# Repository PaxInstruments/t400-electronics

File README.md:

t400-electronics
================

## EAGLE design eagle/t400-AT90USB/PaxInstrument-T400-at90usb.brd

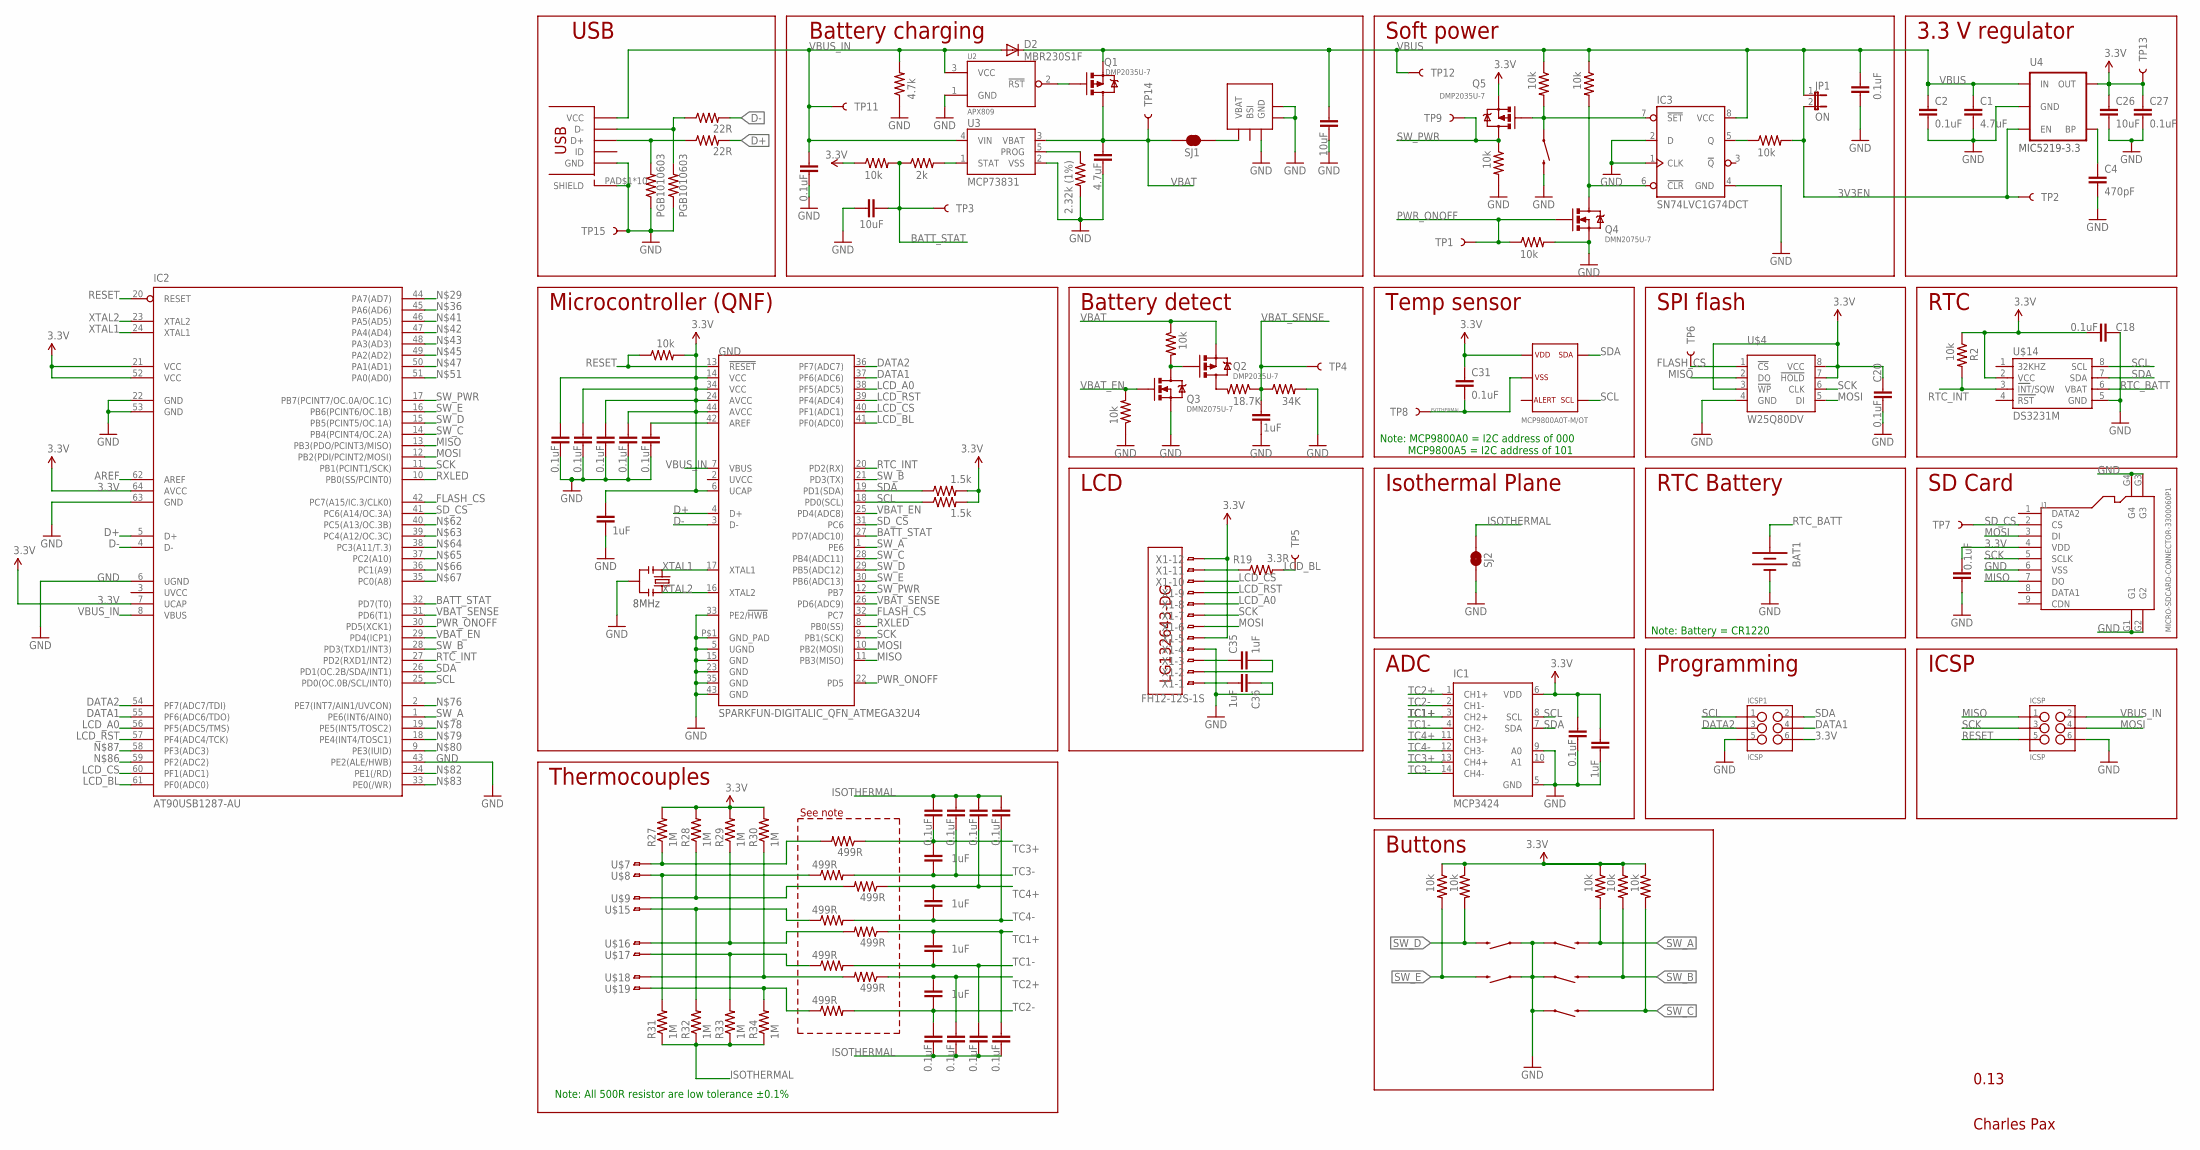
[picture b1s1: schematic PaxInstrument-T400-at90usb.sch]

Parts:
BAT1: BATTERY12MM; BATTCON_12MM; MPN 3000TR
C1, C9: 4.7uF; SPARKFUN-CAPACITORS_0603-CAP
C2, C3, C5, C6, C13, C14, C15, C16, C17, C18, C20, C21, C24, C25, C27, C28, C29, C31, C32, C33, C34, C37: 0.1uF; SPARKFUN-CAPACITORS_0603-CAP
C4: 470pF; SPARKFUN-CAPACITORS_0603-CAP
C7, C8, C10, C11, C19, C23, C30, C35, C36: 1uF; SPARKFUN-CAPACITORS_0603-CAP
C12, C22, C26: 10uF; SPARKFUN-CAPACITORS_0603-CAP
D2: MBR230S1F; SOD123; MPN MBR230S1F-7
GND: SPARKFUN-DIGITALIC_QFN_ATMEGA32U4; SPARKFUN-DIGITALIC_SPARKFUN-DIGITALIC_QFN-44; MPN ATMEGA32U4-MU
IC1: MCP3424; SO14; MPN MCP3424-E/SL
IC2: AT90USB1287-AU; TQFP64
IC3: SN74LVC1G74DCT; SSOP8; MPN SN74LVC1G74DCTR
ICSP, ICSP1: ICSP; SPARKFUN-CONNECTORS_2X3_SMT_POSTS_PAXINSTRUMENT; MPN 95278-101A06LF
J1: MICRO-SDCARD-CONNECTOR-3300060P1; 9P-SMD-W-RING; MPN ST-TF-003A
JP1: ON; SJ_2S-NO; MPN N/A
Q1, Q2, Q5: DMP2035U-7; SOT23; MPN DMP2035U-7
Q3, Q4: DMN2075U-7; SOT23; MPN DMN2075U-7
R1, R2, R4, R5, R6, R7, R8, R11, R12, R15, R16, R18, R21, R22, R23: 10k; SPARKFUN-RESISTORS_0603-RES
R3: 2.32k (1%); SPARKFUN-RESISTORS_0603-RES
R9, R10: 22R; SPARKFUN-RESISTORS_0603-RES
R13, R14: 1.5k; SPARKFUN-RESISTORS_0603-RES
R17: 2k; SPARKFUN-RESISTORS_0603-RES
R19: 3.3R; SPARKFUN-RESISTORS_0603-RES
R20: 18.7K; SPARKFUN-RESISTORS_0603-RES
R24: 34K; SPARKFUN-RESISTORS_0603-RES
R25: 4.7k; SPARKFUN-RESISTORS_0603-RES
R27, R28, R29, R30, R31, R32, R33, R34: 1M; SPARKFUN-RESISTORS_0603-RES
R35, R36, R37, R38, R39, R40, R41, R42: 499R; SPARKFUN-RESISTORS_0603-RES; MPN TNPW0603499RBEEA
S1, S2, S3, S4, S5, S6: SWITCH-MOMENTARY-2SMD; TACTILE_SWITCH_SMD; MPN RS-187R05A2-DS MT RT
SJ1, SJ2: JUMPER-PAD-2-NC_BY_TRACE; PAD-JUMPER-2-NC_BY_TRACE_YES_SILK; MPN N/A
TP1: PWR_ONOFF; TP_15TH; MPN N/A
TP2: 3V3_EN; TP_15TH; MPN N/A
TP3: BATT_STAT; TP_15TH; MPN N/A
TP4: VBAT_SENSE; TP_15TH; MPN N/A
TP5: LCD_BL; TP_15TH; MPN N/A
TP6: FLASH_CS; TP_15TH; MPN N/A
TP7: SD_CS; TP_15TH; MPN N/A
TP8: ISOTHERMAL; TP_15TH; MPN N/A
TP9: SW_PWR; TP_15TH; MPN N/A
TP11: VBUS_IN; TP_15TH; MPN N/A
TP12: VBUS; TP_15TH; MPN N/A
TP13: 3.3V; TP_15TH; MPN N/A
TP14: VBAT; TP_15TH; MPN N/A
TP15: GND; TP_15TH; MPN N/A
U1: MCP9800; SOT23-5L; MPN MCP9800A0T-M/OT
U2: APX809; SOT23; MPN APX809-44SAG-7
U3: MCP73831; SOT23-5; MPN MCP73832T-2DCI/OT
U4: MIC5219-3.3V; SOT23-5; MPN MIC5219-3.3YM5 TR
U$1: USB_MICROSMT+THRUHULE; USB_MICRO_THRUHOLE; MPN 10118194-0001LF
U$2: BL-5C-CONNECTOR; MPN BC-4-3P (77H)
U$4: W25Q80DV; CHARLESPAX_SOIC8M; MPN W25Q80DVSSIG-ND
U$5: LG132643-DG; MPN LG132643-DW
U$7, U$8, U$9, U$15, U$16, U$17, U$18, U$19: TC-MINI-SINGLE; TC-CLIP-SINGLE
U$14: DS3231M; SOIC8; MPN DS3231MZ+
X1: FH12-12S-1S; FH12-12S-1SH; MPN FH12-12S-1SH(55)
Y1: RESONATORSMD; RESONATOR-SMD; MPN CSTCE8M00G52-R0
Z1, Z2: PGB1010603; SPARKFUN-RESISTORS_0603-RES; MPN PGB1010603NRHF

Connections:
3.3V: C5.1, C18.1, C19.1, C20.2, C21.2, C26.1, C27.1, C29.1, C30.1, C31.1, C32.1, C33.1, C34.1, GND.6 (UCAP), GND.14 (VCC), GND.24 (AVCC), GND.34 (VCC), GND.44 (AVCC), IC1.6 (VDD), IC2.7 (UCAP), IC2.21 (VCC), IC2.52 (VCC), IC2.64 (AVCC), ICSP1.6, J1.4 (VDD), Q5.2 (S), R1.1, R2.1, R4.2, R8.1, R11.1, R12.1, R13.2, R14.2, R15.1, R16.1, R27.2, R28.2, R29.2, R30.2, TP13.P$1, U1.1, U4.5 (OUT), U$4.3 (!WP), U$4.7 (!HOLD), U$4.8 (VCC), U$14.2 (VCC), X1.5, X1.12
3V3EN: JP1.2, R21.2, TP2.P$1, U4.3 (EN)
AREF: C3.1, GND.42 (AREF), IC2.62 (AREF)
BATT_STAT: C22.1, GND.27 (PD7(ADC10)), IC2.32 (PD7(T0)), R1.2, R17.1, TP3.P$1
D+: GND.4 (D+), IC2.5 (D+), R9.2
D-: GND.3 (D-), IC2.4 (D-), R10.2
DATA1: GND.37 (PF6(ADC6)), IC2.55 (PF6(ADC6/TDO)), ICSP1.4
DATA2: GND.36 (PF7(ADC7)), IC2.54 (PF7(ADC7/TDI)), ICSP1.3
FLASH_CS: GND.32 (PC7), IC2.42 (PC7(A15/IC.3/CLK0)), TP6.P$1, U$4.1 (!CS)
GND: BAT1.GND (-), C1.2, C2.2, C3.2, C4.2, C5.2, C6.2, C9.2, C12.2, C18.2, C19.2, C20.1, C21.1, C22.2, C23.2, C26.2, C27.2, C28.2, C29.2, C30.2, C32.2, C33.2, C34.2, C36.1, GND.5 (UGND), GND.15 (GND), GND.23 (GND), GND.33 (PE2/!HWB), GND.35 (GND), GND.43 (GND), GND.P$1 (GND_PAD), IC1.5 (GND), IC1.9 (A0), IC2.6 (UGND), IC2.22 (GND), IC2.43 (PE2(ALE/HWB)), IC2.53 (GND), IC2.63 (GND), IC3.1 (CLK), IC3.2 (D), IC3.4 (GND), ICSP.6, ICSP1.5, J1.6 (VSS), J1.G1, J1.G2, J1.G3, J1.G4, Q3.2 (S), Q4.2 (S), R3.2, R18.2, R22.2, R23.1, R24.2, R25.1, S1.1, S2.1, S3.1, S4.1, S5.1, S6.3 (2), SJ2.1, TP15.P$1, U2.1 (GND), U3.2 (VSS), U4.2 (GND), U$1.PAD$1 (SHIELD), U$1.PAD$2 (SHIELD), U$1.PAD$3 (SHIELD), U$1.PAD$4 (SHIELD), U$1.PAD$5 (SHIELD), U$1.PAD$6 (SHIELD), U$1.PAD$7 (SHIELD), U$1.PAD$8 (SHIELD), U$1.PAD$9 (SHIELD), U$1.PAD$10 (SHIELD), U$1.PIN$5 (GND), U$2.P$3 (GND), U$2.P$4, U$2.P$5, U$4.4 (GND), U$14.5 (GND), X1.4, Y1.2, Z1.1, Z2.1
ISOTHERMAL: C13.2, C14.2, C15.2, C16.2, C17.1, C24.1, C25.1, C31.2, C37.1, R31.1, R32.1, R33.1, R34.1, SJ2.2, TP8.P$1, U1.2
LCD_A0: GND.38 (PF5(ADC5)), IC2.56 (PF5(ADC5/TMS)), X1.8
LCD_BL: GND.41 (PF0(ADC0)), IC2.61 (PF0(ADC0)), R19.2, TP5.P$1
LCD_CS: GND.40 (PF1(ADC1)), IC2.60 (PF1(ADC1)), X1.10
LCD_RST: GND.39 (PF4(ADC4)), IC2.57 (PF4(ADC4/TCK)), X1.9
MISO: GND.11 (PB3(MISO)), IC2.13 (PB3(PDO/PCINT3/MISO)), ICSP.1, J1.7 (DO), U$4.2 (DO)
MOSI: GND.10 (PB2(MOSI)), IC2.12 (PB2(PDI/PCINT2/MOSI)), ICSP.4, J1.3 (DI), U$4.5 (DI), X1.6
unnamed: C4.1, U4.4 (BP)
unnamed: R17.2, U3.1 (STAT)
unnamed: R19.1, X1.11
unnamed: R31.2, R36.1, U$8.P$1
unnamed: R3.1, U3.5 (PROG)
unnamed: SJ1.2, U$2.P$1 (VBAT)
unnamed: R27.1, R35.2, U$7.P$1
unnamed: Q1.1 (G), U2.2 (!RST)
unnamed: R29.1, R39.2, U$16.P$1
unnamed: R33.2, R41.1, U$17.P$1
unnamed: R34.2, R42.1, U$19.P$1
unnamed: Q2.3 (D), R20.2
unnamed: IC3.7 (!SET), Q5.1 (G), R6.2, S6.1
unnamed: Q2.1 (G), Q3.3 (D), R5.2
unnamed: IC3.6 (!CLR), Q4.3 (D), R7.2
unnamed: IC3.5 (Q), R21.1
unnamed: R10.1, U$1.PIN$2 (D-), Z2.2
unnamed: R9.1, U$1.PIN$3 (D+), Z1.2
unnamed: R32.2, R38.1, U$15.P$1
unnamed: R28.1, R37.2, U$9.P$1
unnamed: C35.1, X1.3
unnamed: C35.2, X1.2
unnamed: C36.2, X1.1
unnamed: R30.1, R40.2, U$18.P$1
PWR_ONOFF: GND.22 (PD5), IC2.30 (PD5(XCK1)), Q4.1 (G), R22.1, TP1.P$1
RESET: GND.13 (!RESET), IC2.20 (RESET), ICSP.5, R4.1
RTC_BATT: BAT1.PWR@1 (+), U$14.6 (VBAT)
RTC_INT: GND.20 (PD2(RX)), IC2.27 (PD2(RXD1/INT2)), R2.2, U$14.3 (INT/SQW)
RXLED: GND.8 (PB0(SS)), IC2.10 (PB0(SS/PCINT0))
SCK: GND.9 (PB1(SCK)), IC2.11 (PB1(PCINT1/SCK)), ICSP.3, J1.5 (SCLK), U$4.6 (CLK), X1.7
SCL: GND.18 (PD0(SCL)), IC1.8 (SCL), IC2.25 (PD0(OC.0B/SCL/INT0)), ICSP1.1, R14.1, U1.4, U$14.8 (SCL)
SDA: GND.19 (PD1(SDA)), IC1.7 (SDA), IC2.26 (PD1(OC.2B/SDA/INT1)), ICSP1.2, R13.1, U1.5, U$14.7 (SDA)
SD_CS: GND.31 (PC6), IC2.41 (PC6(A14/OC.3A)), J1.2 (CS), TP7.P$1
SW_A: GND.1 (PE6), IC2.1 (PE6(INT6/AIN0)), R8.2, S3.3 (2)
SW_B: GND.21 (PD3(TX)), IC2.28 (PD3(TXD1/INT3)), R11.2, S2.3 (2)
SW_C: GND.28 (PB4(ADC11)), IC2.14 (PB4(PCINT4/OC.2A)), R12.2, S1.3 (2)
SW_D: GND.29 (PB5(ADC12)), IC2.15 (PB5(PCINT5/OC.1A)), R15.2, S4.3 (2)
SW_E: GND.30 (PB6(ADC13)), IC2.16 (PB6(PCINT6/OC.1B)), R16.2, S5.3 (2)
SW_PWR: GND.12 (PB7), IC2.17 (PB7(PCINT7/OC.0A/OC.1C)), Q5.3 (D), R18.1, TP9.P$1
TC1+: C10.1, C16.1, IC1.3 (CH2+), R39.1
TC1-: C10.2, C15.1, IC1.4 (CH2-), R41.2
TC2+: C11.1, C14.1, IC1.1 (CH1+), R40.1
TC2-: C11.2, C13.1, IC1.2 (CH1-), R42.2
TC3+: C7.1, C17.2, IC1.13 (CH4+), R35.1
TC3-: C7.2, C24.2, IC1.14 (CH4-), R36.2
TC4+: C8.1, C25.2, IC1.11 (CH3+), R37.1
TC4-: C8.2, C37.2, IC1.12 (CH3-), R38.2
UVCC: IC2.3 (UVCC)
VBAT: C9.1, Q1.3 (D), Q2.2 (S), R5.1, SJ1.1, TP14.P$1, U3.3 (VBAT)
VBAT_EN: GND.25 (PD4(ADC8)), IC2.29 (PD4(ICP1)), Q3.1 (G), R23.2
VBAT_SENSE: C23.1, GND.26 (PD6(ADC9)), IC2.31 (PD6(T1)), R20.1, R24.1, TP4.P$1
VBUS: C1.1, C2.1, C12.1, C28.1, D2.C, IC3.8 (VCC), JP1.1, Q1.2 (S), R6.1, R7.1, TP12.P$1, U4.1 (IN)
VBUS_IN: C6.1, D2.A, GND.7 (VBUS), IC2.8 (VBUS), ICSP.2, R25.2, TP11.P$1, U2.3 (VCC), U3.4 (VIN), U$1.PIN$1 (VCC)
XTAL1: GND.17 (XTAL1), IC2.24 (XTAL1), Y1.1
XTAL2: GND.16 (XTAL2), IC2.23 (XTAL2), Y1.3

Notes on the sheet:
MIC5219-3.3
8MHz
ADC
USB
Battery charging
Soft power
3.3 V regulator
RTC
LCD
Buttons
Microcontroller (QNF)
ICSP
Temp sensor
0.13
Programming
Isothermal Plane
Thermocouples
RTC Battery
Charles Pax
SPI flash
SD Card
Battery detect
Note: MCP9800A0 = I2C address of 000 MCP9800A5 = I2C address of 101
Note: All 500R resistor are low tolerance ±0.1%
See note
Note: Battery = CR1220

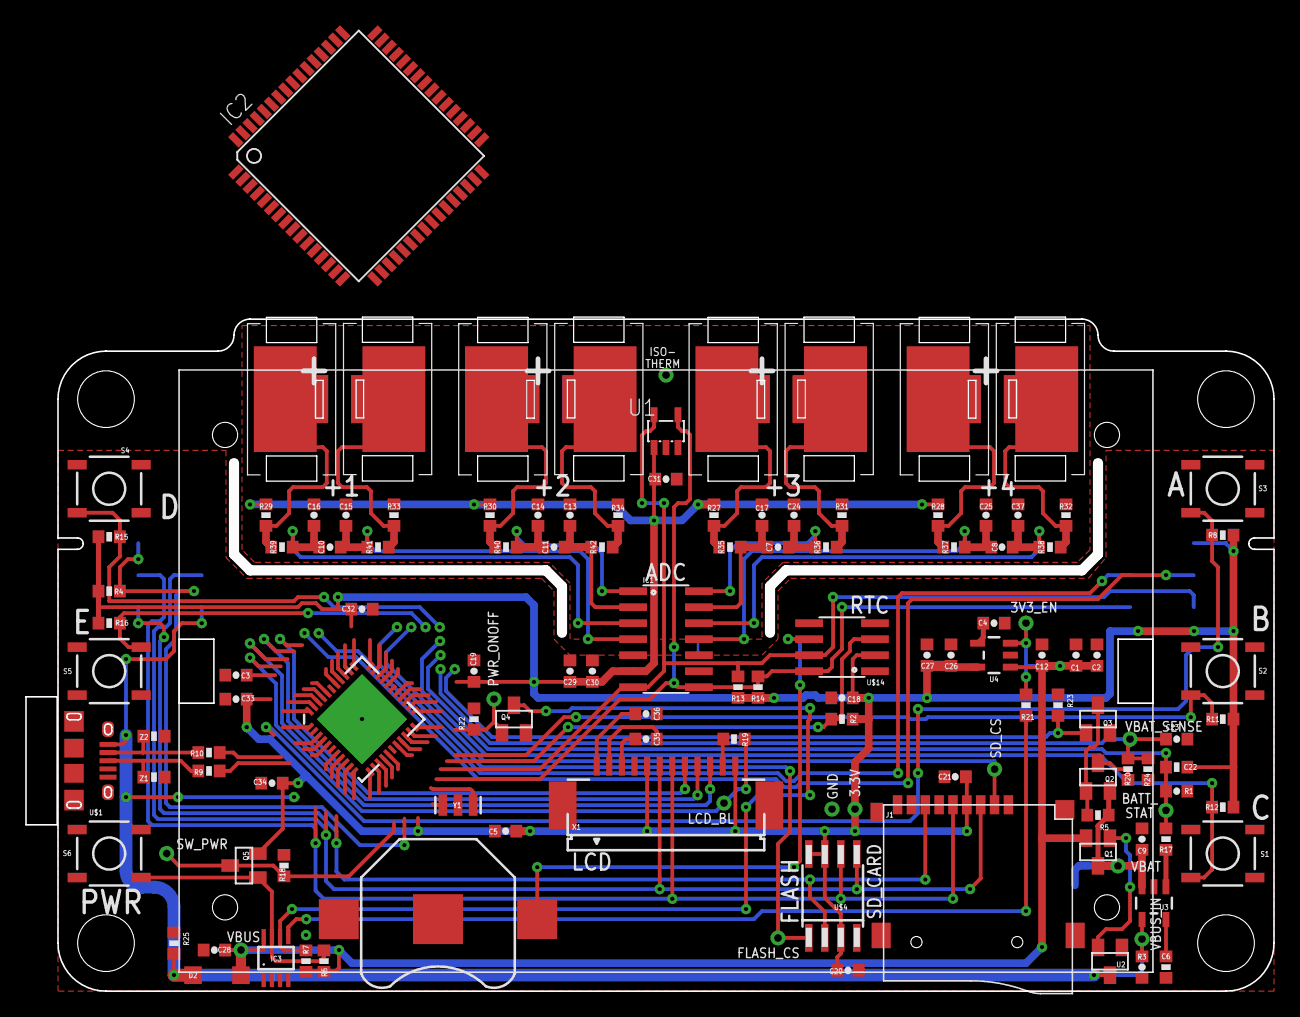
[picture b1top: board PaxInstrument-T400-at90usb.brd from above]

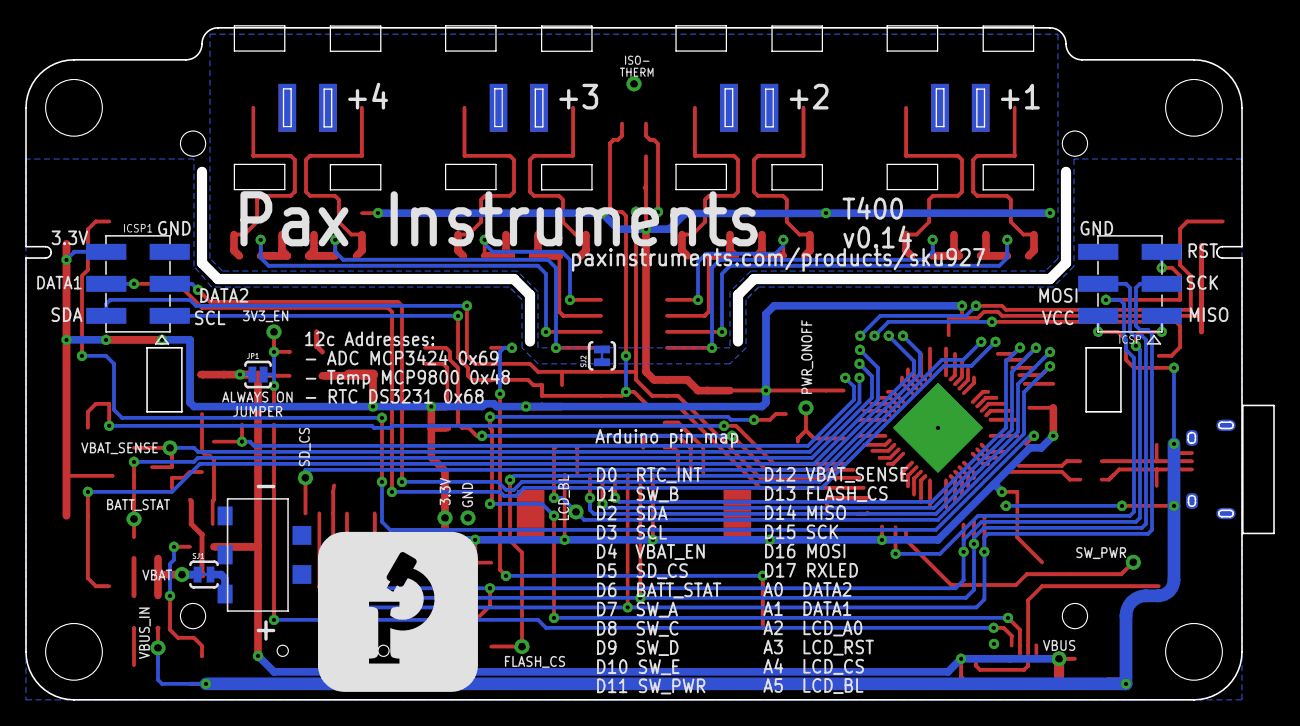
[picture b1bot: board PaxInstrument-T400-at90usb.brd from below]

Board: 4 copper layers, 99.1 x 53.5 mm, 137 parts (11 on the bottom side), 71 nets.

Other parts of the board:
U$6: PAX-LOGO-0.5IN

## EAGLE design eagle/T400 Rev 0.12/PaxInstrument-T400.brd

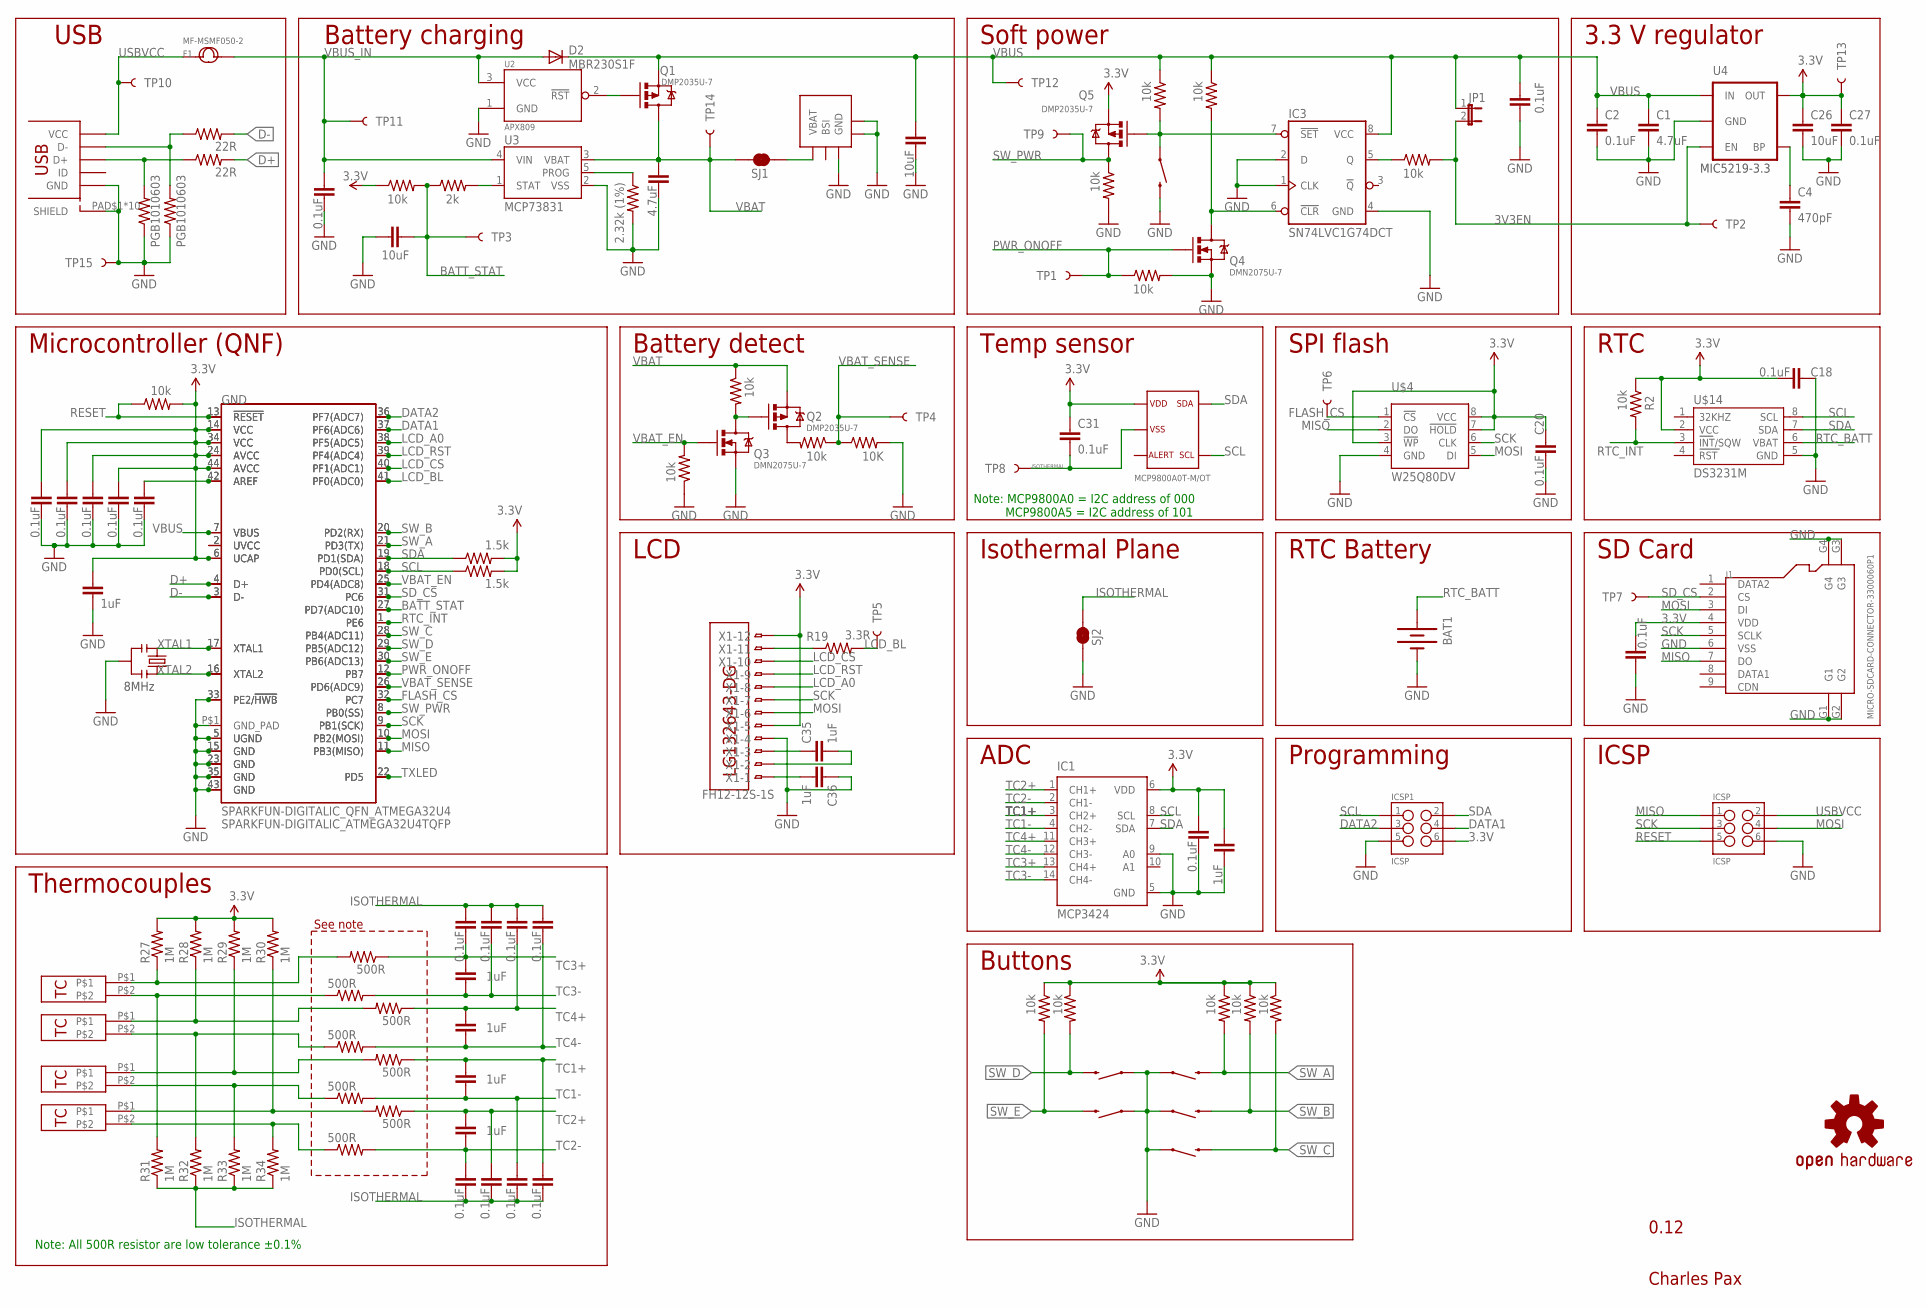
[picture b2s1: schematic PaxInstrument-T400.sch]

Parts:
BAT1: BATTERY12MM; BATTCON_12MM; MPN 3000TR
C1, C9: 4.7uF; SPARKFUN-CAPACITORS_0603-CAP
C2, C3, C5, C6, C13, C14, C15, C16, C17, C18, C20, C21, C24, C25, C27, C28, C29, C31, C32, C33, C34, C37: 0.1uF; SPARKFUN-CAPACITORS_0603-CAP
C4: 470pF; SPARKFUN-CAPACITORS_0603-CAP
C7, C8, C10, C11, C19, C30, C35, C36: 1uF; SPARKFUN-CAPACITORS_0603-CAP
C12, C22, C26: 10uF; SPARKFUN-CAPACITORS_0603-CAP
D2: MBR230S1F; SOD123; MPN MBR230S1F-7
F1: FUSE-1812; F1812; MPN MF-MSMF050-2
GND: SPARKFUN-DIGITALIC_QFN_ATMEGA32U4; SPARKFUN-DIGITALIC_SPARKFUN-DIGITALIC_QFN-44; MPN ATMEGA32U4-MU
IC1: MCP3424; SO14; MPN MCP3424-E/SL
IC3: SN74LVC1G74DCT; SSOP8; MPN SN74LVC1G74DCTR
ICSP, ICSP1: ICSP; SPARKFUN-CONNECTORS_2X3_SMT_POSTS_PAXINSTRUMENT; MPN 95278-101A06LF
J1: MICRO-SDCARD-CONNECTOR-3300060P1; 9P-SMD-W-RING; MPN ST-TF-003A
JP1: JUMPER-2SMD-NO; SJ_2S-NO; MPN N/A
LOGO1: OSHW-LOGOS; OSHW-LOGO-S; MPN N/A
Q1, Q2, Q5: DMP2035U-7; SOT23; MPN DMP2035U-7
Q3, Q4: DMN2075U-7; SOT23; MPN DMN2075U-7
R1, R2, R4, R5, R6, R7, R8, R11, R12, R15, R16, R18, R20, R21, R22, R23: 10k; SPARKFUN-RESISTORS_0603-RES
R3: 2.32k (1%); SPARKFUN-RESISTORS_0603-RES
R9, R10: 22R; SPARKFUN-RESISTORS_0603-RES
R13, R14: 1.5k; SPARKFUN-RESISTORS_0603-RES
R17: 2k; SPARKFUN-RESISTORS_0603-RES
R19: 3.3R; SPARKFUN-RESISTORS_0603-RES
R24: 10K; SPARKFUN-RESISTORS_0603-RES
R27, R28, R29, R30, R31, R32, R33, R34: 1M; SPARKFUN-RESISTORS_0603-RES
R35, R36, R37, R38, R39, R40, R41, R42: 500R; SPARKFUN-RESISTORS_0603-RES; MPN RN732ATTD5000B25
S1, S2, S3, S4, S5, S6: SWITCH-MOMENTARY-2SMD; TACTILE_SWITCH_SMD; MPN RS-187R05A2-DS MT RT
SJ1, SJ2: JUMPER-PAD-2-NC_BY_TRACE; PAD-JUMPER-2-NC_BY_TRACE_YES_SILK; MPN N/A
TP1: PWR_ONOFF; TP_15TH; MPN N/A
TP2: 3V3_EN; TP_15TH; MPN N/A
TP3: BATT_STAT; TP_15TH; MPN N/A
TP4: VBAT_SENSE; TP_15TH; MPN N/A
TP5: LCD_BL; TP_15TH; MPN N/A
TP6: FLASH_CS; TP_15TH; MPN N/A
TP7: SD_CS; TP_15TH; MPN N/A
TP8: ISOTHERMAL; TP_15TH; MPN N/A
TP9: SW_PWR; TP_15TH; MPN N/A
TP10: TEST-POINTTP_15TH_THRU; TP_15TH; MPN N/A
TP11: VBUS_IN; TP_15TH; MPN N/A
TP12: VBUS; TP_15TH; MPN N/A
TP13: 3.3V; TP_15TH; MPN N/A
TP14: VBAT; TP_15TH; MPN N/A
TP15: GND; TP_15TH; MPN N/A
U1: MCP9800; SOT23-5L; MPN MCP9800A0T-M/OT
U2: APX809; SOT23; MPN APX809-44SAG-7
U3: MCP73831; SOT23-5; MPN MCP73832T-2DCI/OT
U4: MIC5219-3.3V; SOT23-5; MPN MIC5219-3.3YM5 TR
U$1: USB_MICROSMT+THRUHULE; USB_MICRO_THRUHOLE; MPN 10118194-0001LF
U$2: BL-5C-CONNECTOR
U$3: SPARKFUN-DIGITALIC_ATMEGA32U4TQFP; SPARKFUN-DIGITALIC_SPARKFUN-DIGITALIC_TQFP44; MPN ATMEGA32U4-AU
U$4: W25Q80DV; CHARLESPAX_SOIC8M; MPN W25Q80DVSSIG-ND
U$5: LG132643-DG; MPN LG132643-DW
U$10, U$11, U$12, U$13: CHARLESPAX_TC-MINI-CONNECTOR; MPN 3572
U$14: DS3231M; SOIC8; MPN DS3231MZ+
X1: FH12-12S-1S; FH12-12S-1SH; MPN FH12-12S-1SH(55)
Y1: RESONATORSMD; RESONATOR-SMD; MPN CSTCE8M00G52-R0
Z1, Z2: PGB1010603; SPARKFUN-RESISTORS_0603-RES; MPN PGB1010603NRHF

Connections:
3.3V: C5.1, C18.1, C19.1, C20.2, C21.2, C26.1, C27.1, C29.1, C30.1, C31.1, C32.1, C33.1, C34.1, GND.6 (UCAP), GND.14 (VCC), GND.24 (AVCC), GND.34 (VCC), GND.44 (AVCC), IC1.6 (VDD), ICSP1.6, J1.4 (VDD), Q5.2 (S), R1.1, R2.1, R4.2, R8.1, R11.1, R12.1, R13.2, R14.2, R15.1, R16.1, R27.2, R28.2, R29.2, R30.2, TP13.P$1, U1.1, U4.5 (OUT), U$3.6 (UCAP), U$3.14 (VCC), U$3.24 (AVCC), U$3.34 (VCC), U$3.44 (AVCC), U$4.3 (!WP), U$4.7 (!HOLD), U$4.8 (VCC), U$14.2 (VCC), X1.5, X1.12
3V3EN: JP1.2, R21.2, TP2.P$1, U4.3 (EN)
BATT_STAT: C22.1, GND.27 (PD7(ADC10)), R1.2, R17.1, TP3.P$1, U$3.27 (PD7(ADC10))
D+: GND.4 (D+), R9.2, U$3.4 (D+)
D-: GND.3 (D-), R10.2, U$3.3 (D-)
DATA1: GND.37 (PF6(ADC6)), ICSP1.4, U$3.37 (PF6(ADC6))
DATA2: GND.36 (PF7(ADC7)), ICSP1.3, U$3.36 (PF7(ADC7))
FLASH_CS: GND.32 (PC7), TP6.P$1, U$3.32 (PC7), U$4.1 (!CS)
GND: BAT1.GND (-), C1.2, C2.2, C3.2, C4.2, C5.2, C6.2, C9.2, C12.2, C18.2, C19.2, C20.1, C21.1, C22.2, C26.2, C27.2, C28.2, C29.2, C30.2, C32.2, C33.2, C34.2, C36.1, GND.5 (UGND), GND.15 (GND), GND.23 (GND), GND.33 (PE2/!HWB), GND.35 (GND), GND.43 (GND), GND.P$1 (GND_PAD), IC1.5 (GND), IC1.9 (A0), IC3.1 (CLK), IC3.2 (D), IC3.4 (GND), ICSP.6, ICSP1.5, J1.6 (VSS), J1.G1, J1.G2, J1.G3, J1.G4, Q3.2 (S), Q4.2 (S), R3.2, R18.2, R22.2, R23.1, R24.2, S1.1, S2.1, S3.1, S4.1, S5.1, S6.3 (2), SJ2.1, TP15.P$1, U2.1 (GND), U3.2 (VSS), U4.2 (GND), U$1.PAD$1 (SHIELD), U$1.PAD$2 (SHIELD), U$1.PAD$3 (SHIELD), U$1.PAD$4 (SHIELD), U$1.PAD$5 (SHIELD), U$1.PAD$6 (SHIELD), U$1.PAD$7 (SHIELD), U$1.PAD$8 (SHIELD), U$1.PAD$9 (SHIELD), U$1.PAD$10 (SHIELD), U$1.PIN$5 (GND), U$2.P$3 (GND), U$2.P$4, U$2.P$5, U$3.5 (UGND), U$3.15 (GND), U$3.23 (GND), U$3.33 (PE2/!HWB), U$3.35 (GND), U$3.43 (GND), U$4.4 (GND), U$14.5 (GND), X1.4, Y1.2, Z1.1, Z2.1
ISOTHERMAL: C13.2, C14.2, C15.2, C16.2, C17.1, C24.1, C25.1, C31.2, C37.1, R31.1, R32.1, R33.1, R34.1, SJ2.2, TP8.P$1, U1.2
LCD_A0: GND.38 (PF5(ADC5)), U$3.38 (PF5(ADC5)), X1.8
LCD_BL: GND.41 (PF0(ADC0)), R19.2, TP5.P$1, U$3.41 (PF0(ADC0))
LCD_CS: GND.40 (PF1(ADC1)), U$3.40 (PF1(ADC1)), X1.10
LCD_RST: GND.39 (PF4(ADC4)), U$3.39 (PF4(ADC4)), X1.9
MISO: GND.11 (PB3(MISO)), ICSP.1, J1.7 (DO), U$3.11 (PB3(MISO)), U$4.2 (DO)
MOSI: GND.10 (PB2(MOSI)), ICSP.4, J1.3 (DI), U$3.10 (PB2(MOSI)), U$4.5 (DI), X1.6
unnamed: C4.1, U4.4 (BP)
unnamed: R17.2, U3.1 (STAT)
unnamed: R19.1, X1.11
unnamed: R31.2, R36.1, U$10.P$2
unnamed: R3.1, U3.5 (PROG)
unnamed: SJ1.2, U$2.P$1 (VBAT)
unnamed: R27.1, R35.2, U$10.P$1
unnamed: Q1.1 (G), U2.2 (!RST)
unnamed: R29.1, R39.2, U$12.P$1
unnamed: R33.2, R41.1, U$12.P$2
unnamed: C3.1, GND.42 (AREF), U$3.42 (AREF)
unnamed: R34.2, R42.1, U$13.P$2
unnamed: GND.2 (UVCC), U$3.2 (UVCC)
unnamed: Q2.3 (D), R20.2
unnamed: IC3.7 (!SET), Q5.1 (G), R6.2, S6.1
unnamed: Q2.1 (G), Q3.3 (D), R5.2
unnamed: IC3.6 (!CLR), Q4.3 (D), R7.2
unnamed: IC3.5 (Q), R21.1
unnamed: R10.1, U$1.PIN$2 (D-), Z2.2
unnamed: R9.1, U$1.PIN$3 (D+), Z1.2
unnamed: R32.2, R38.1, U$11.P$2
unnamed: R28.1, R37.2, U$11.P$1
unnamed: C35.1, X1.3
unnamed: C35.2, X1.2
unnamed: C36.2, X1.1
unnamed: R30.1, R40.2, U$13.P$1
PWR_ONOFF: GND.12 (PB7), Q4.1 (G), R22.1, TP1.P$1, U$3.12 (PB7)
RESET: GND.13 (!RESET), ICSP.5, R4.1, U$3.13 (!RESET)
RTC_BATT: BAT1.PWR@1 (+), U$14.6 (VBAT)
RTC_INT: GND.1 (PE6), R2.2, U$3.1 (PE6), U$14.3 (INT/SQW)
SCK: GND.9 (PB1(SCK)), ICSP.3, J1.5 (SCLK), U$3.9 (PB1(SCK)), U$4.6 (CLK), X1.7
SCL: GND.18 (PD0(SCL)), IC1.8 (SCL), ICSP1.1, R14.1, U1.4, U$3.18 (PD0(SCL)), U$14.8 (SCL)
SDA: GND.19 (PD1(SDA)), IC1.7 (SDA), ICSP1.2, R13.1, U1.5, U$3.19 (PD1(SDA)), U$14.7 (SDA)
SD_CS: GND.31 (PC6), J1.2 (CS), TP7.P$1, U$3.31 (PC6)
SW_A: GND.21 (PD3(TX)), R8.2, S3.3 (2), U$3.21 (PD3(TX))
SW_B: GND.20 (PD2(RX)), R11.2, S2.3 (2), U$3.20 (PD2(RX))
SW_C: GND.28 (PB4(ADC11)), R12.2, S1.3 (2), U$3.28 (PB4(ADC11))
SW_D: GND.29 (PB5(ADC12)), R15.2, S4.3 (2), U$3.29 (PB5(ADC12))
SW_E: GND.30 (PB6(ADC13)), R16.2, S5.3 (2), U$3.30 (PB6(ADC13))
SW_PWR: GND.8 (PB0(SS)), Q5.3 (D), R18.1, TP9.P$1, U$3.8 (PB0(SS))
TC1+: C10.1, C16.1, IC1.3 (CH2+), R39.1
TC1-: C10.2, C15.1, IC1.4 (CH2-), R41.2
TC2+: C11.1, C14.1, IC1.1 (CH1+), R40.1
TC2-: C11.2, C13.1, IC1.2 (CH1-), R42.2
TC3+: C7.1, C17.2, IC1.13 (CH4+), R35.1
TC3-: C7.2, C24.2, IC1.14 (CH4-), R36.2
TC4+: C8.1, C25.2, IC1.11 (CH3+), R37.1
TC4-: C8.2, C37.2, IC1.12 (CH3-), R38.2
TXLED: GND.22 (PD5), U$3.22 (PD5)
USBVCC: F1.1, ICSP.2, TP10.P$1, U$1.PIN$1 (VCC)
VBAT: C9.1, Q1.3 (D), Q2.2 (S), R5.1, SJ1.1, TP14.P$1, U3.3 (VBAT)
VBAT_EN: GND.25 (PD4(ADC8)), Q3.1 (G), R23.2, U$3.25 (PD4(ADC8))
VBAT_SENSE: GND.26 (PD6(ADC9)), R20.1, R24.1, TP4.P$1, U$3.26 (PD6(ADC9))
VBUS: C1.1, C2.1, C12.1, C28.1, D2.C, GND.7 (VBUS), IC3.8 (VCC), JP1.1, Q1.2 (S), R6.1, R7.1, TP12.P$1, U4.1 (IN), U$3.7 (VBUS)
VBUS_IN: C6.1, D2.A, F1.2, TP11.P$1, U2.3 (VCC), U3.4 (VIN)
XTAL1: GND.17 (XTAL1), U$3.17 (XTAL1), Y1.1
XTAL2: GND.16 (XTAL2), U$3.16 (XTAL2), Y1.3

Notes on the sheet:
MIC5219-3.3
8MHz
ADC
USB
Battery charging
Soft power
3.3 V regulator
RTC
LCD
Buttons
Microcontroller (QNF)
ICSP
Temp sensor
0.12
Programming
Isothermal Plane
Thermocouples
RTC Battery
Charles Pax
SPI flash
SD Card
Battery detect
Note: MCP9800A0 = I2C address of 000 MCP9800A5 = I2C address of 101
Note: All 500R resistor are low tolerance ±0.1%
See note

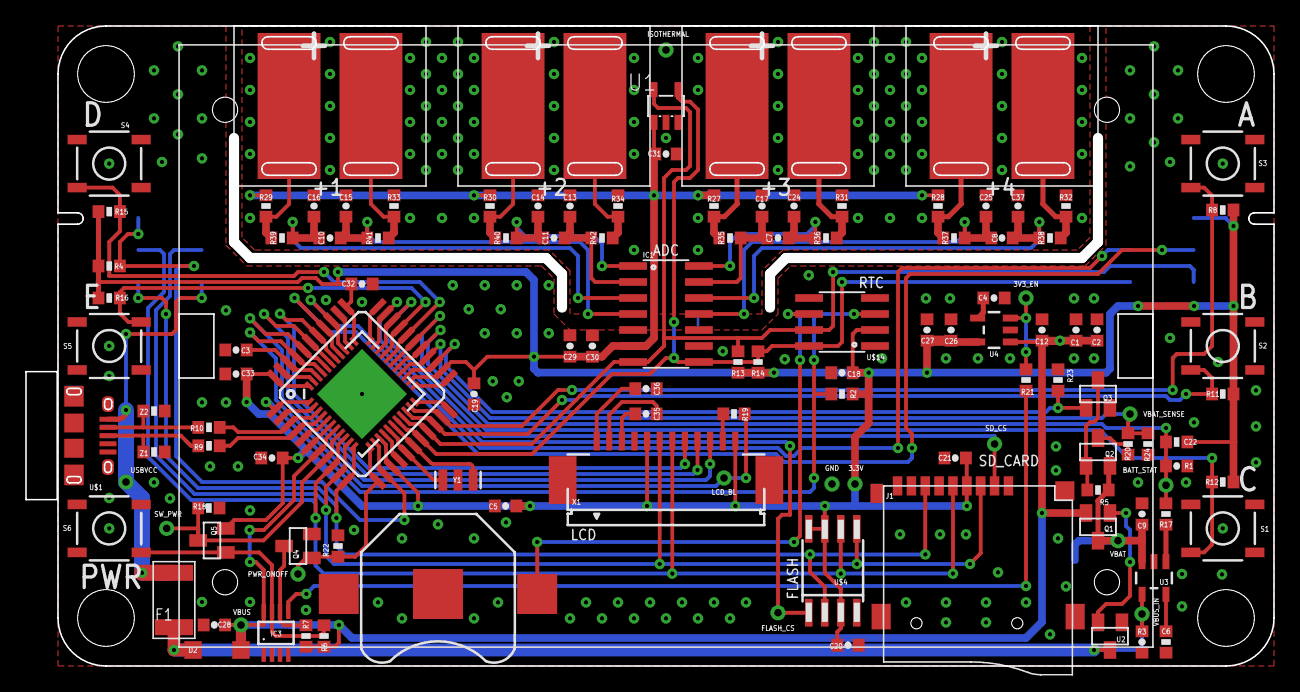
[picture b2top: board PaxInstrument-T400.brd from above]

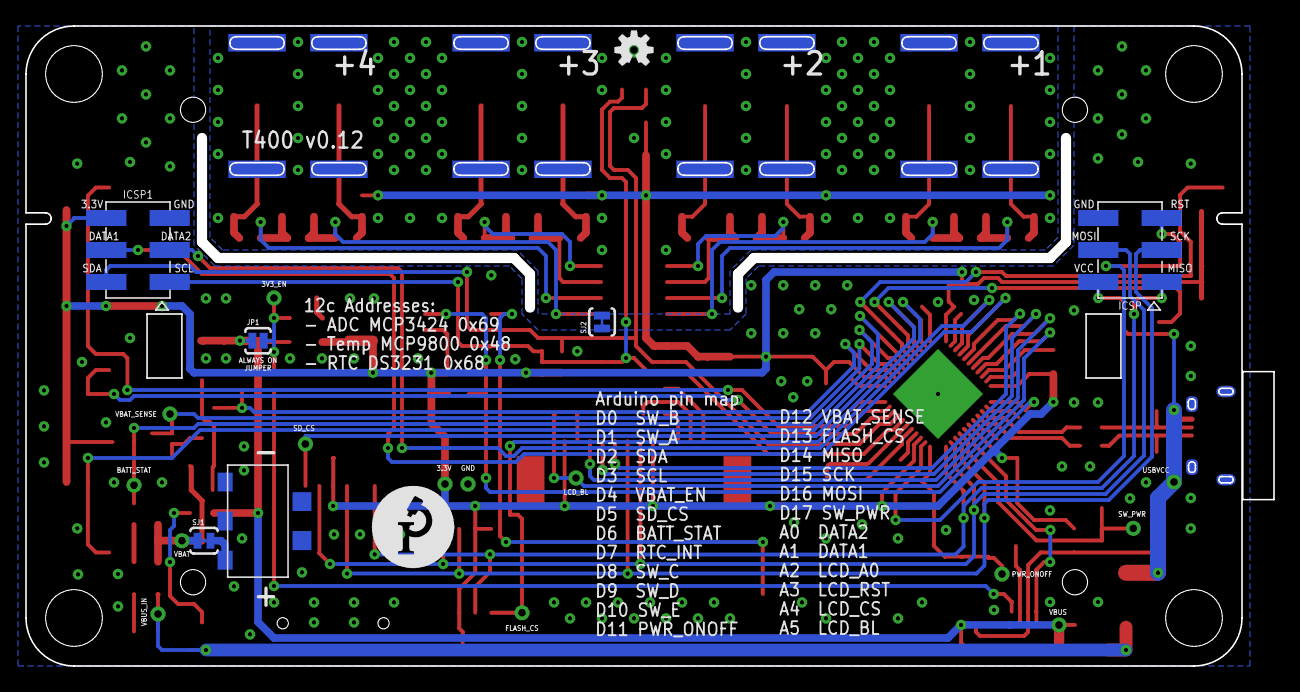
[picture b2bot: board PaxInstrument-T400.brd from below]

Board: 2 copper layers, 99.1 x 50.8 mm, 134 parts (12 on the bottom side), 73 nets.

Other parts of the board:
U$6: PAXINSTRUMENT_LOGO

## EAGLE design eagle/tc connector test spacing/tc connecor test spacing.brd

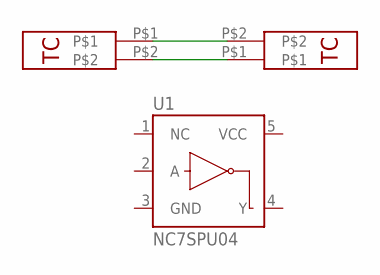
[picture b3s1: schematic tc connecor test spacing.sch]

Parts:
U1: NC7SPU04; SC70
U$1: TC-MINI-INSIDE; TC-CLIP-INSIDE
U$2: TC-MINI-OUTSIDE; TC-CLIP-OUTSIDE

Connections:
unnamed: U$1.P$1, U$2.P$2
unnamed: U$1.P$2, U$2.P$1

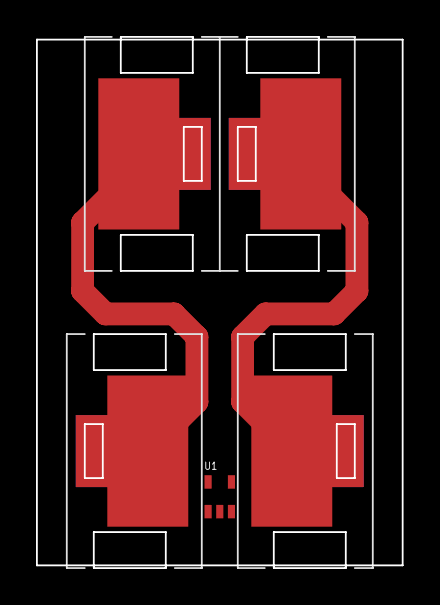
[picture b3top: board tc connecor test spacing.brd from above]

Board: 2 copper layers, 20.3 x 29.2 mm, 3 parts (0 on the bottom side), 2 nets.

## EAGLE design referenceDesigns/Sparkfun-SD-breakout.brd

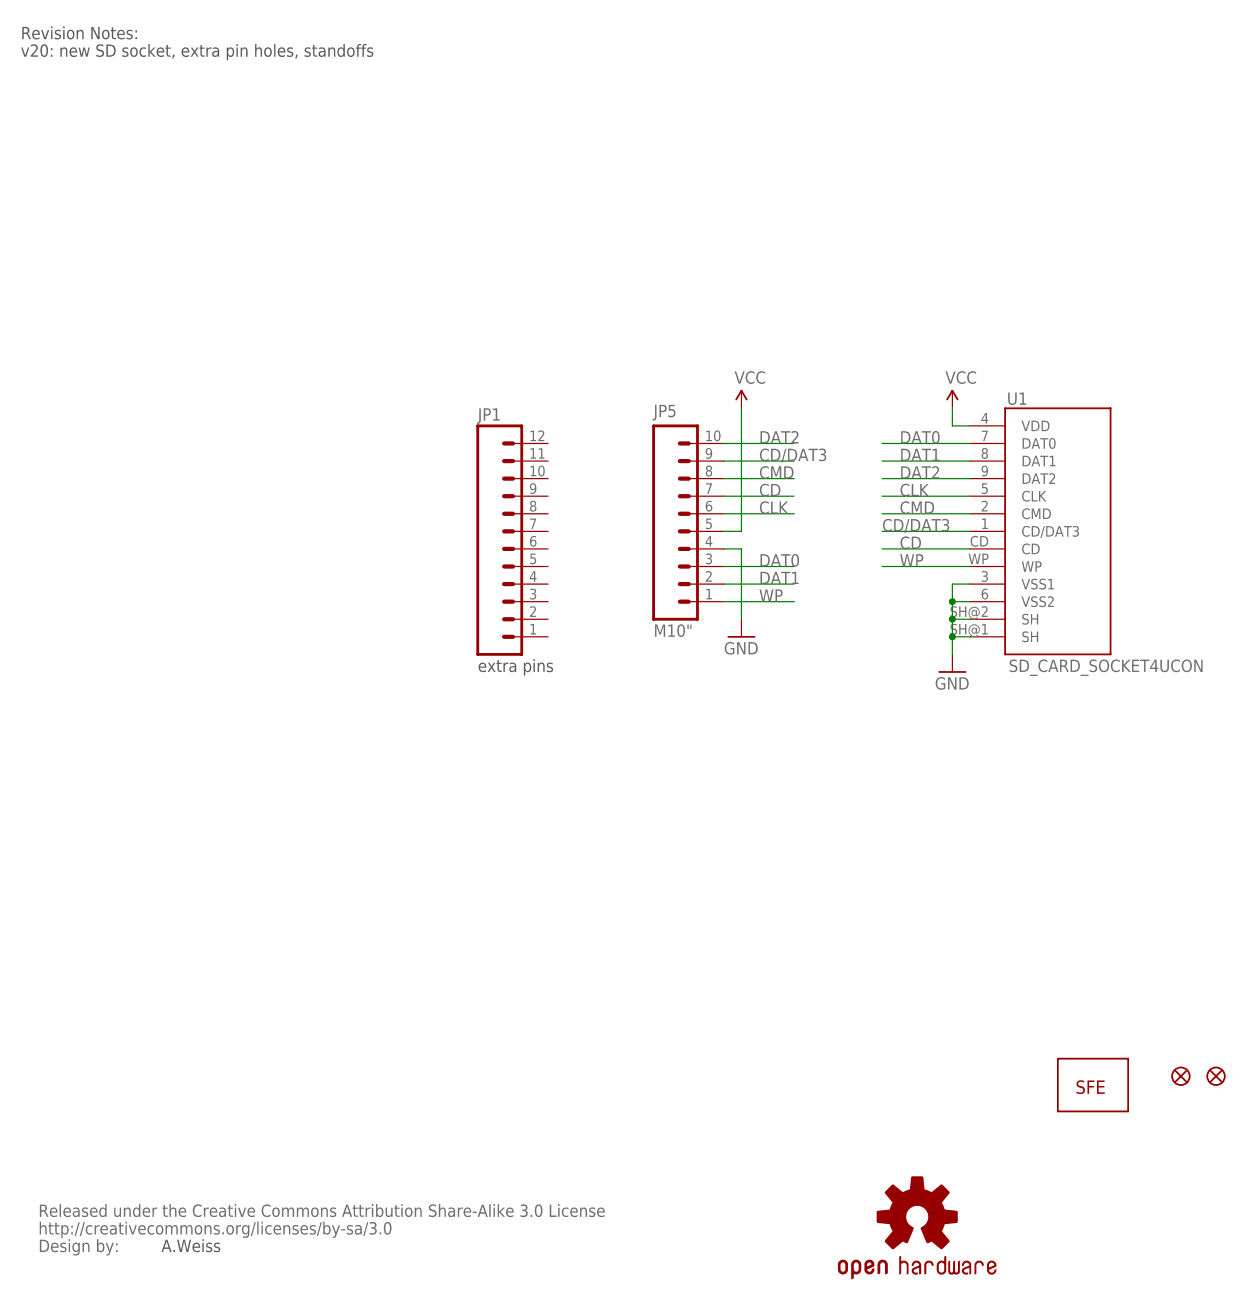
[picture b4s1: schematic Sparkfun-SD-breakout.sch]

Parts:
JP1: M12POGOPIN_HOLES_ONLY; 1X12_HOLES_ONLY
JP2, JP3: FIDUCIALUFIDUCIAL; MICRO-FIDUCIAL
JP5: M10"; 1X10
U1: SD_CARD_SOCKET4UCON; SDCARD_4UCONN
U$1: LOGO-SFENEW; SFE-NEW-WEBLOGO
U$2: CREATIVE_COMMONS
U$3: OSHW-LOGOS; OSHW-LOGO-S

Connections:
CD: JP5.7, U1.CD
CD/DAT3: JP5.9, U1.1 (CD/DAT3)
CLK: JP5.6, U1.5 (CLK)
CMD: JP5.8, U1.2 (CMD)
DAT0: JP5.3, U1.7 (DAT0)
DAT1: JP5.2, U1.8 (DAT1)
DAT2: JP5.10, U1.9 (DAT2)
GND: JP5.4, U1.3 (VSS1), U1.6 (VSS2), U1.SH@1 (SH), U1.SH@2 (SH)
VCC: JP5.5, U1.4 (VDD)
WP: JP5.1, U1.WP

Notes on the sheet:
A.Weiss
Revision Notes:
v20: new SD socket, extra pin holes, standoffs
extra pins

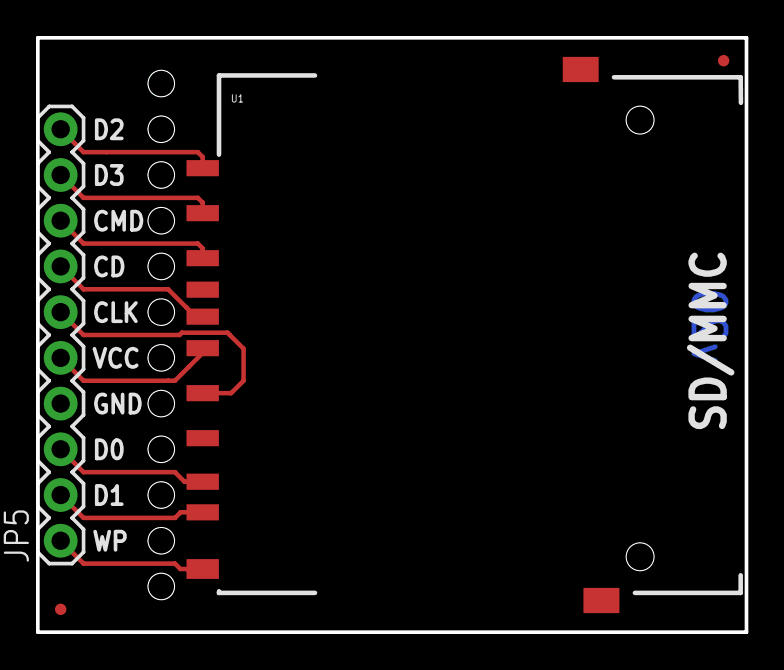
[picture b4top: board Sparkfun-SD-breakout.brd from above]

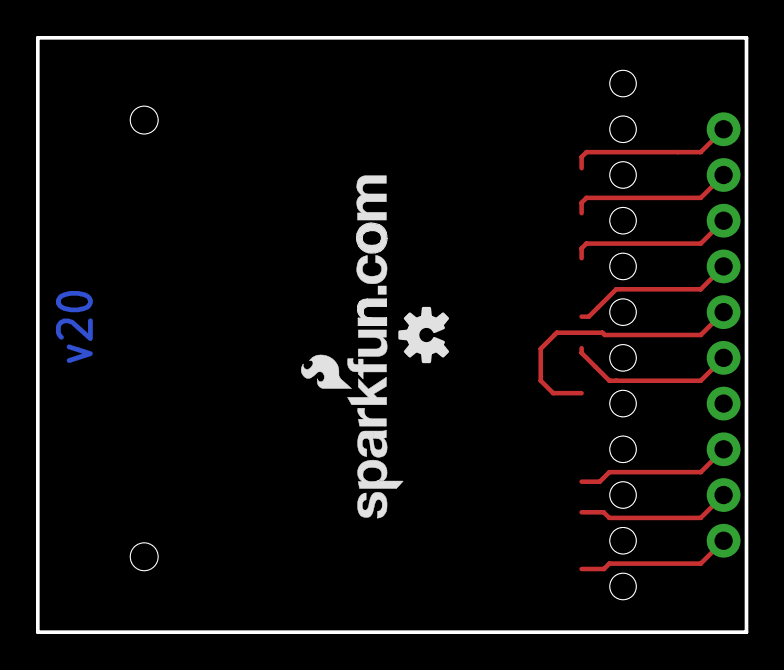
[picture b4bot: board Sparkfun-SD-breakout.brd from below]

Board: 2 copper layers, 39.4 x 33.0 mm, 8 parts (3 on the bottom side), 10 nets.

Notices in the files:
parts and their libraries:
SparkFun-PowerIC: Licensing: CC v3.0 Share-Alike You are welcome to use this library for commercial purposes.
SparkFun-DigitalIC: Licensing: Creative Commons ShareAlike 4.0 International - https://creativecommons.org/licenses/by-sa/4.0
SparkFun-Aesthetics: Creative Commons License summary
